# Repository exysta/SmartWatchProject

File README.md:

# SmartWatch Project

## Overview

This repository hosts the source code and technical documentation for the SmartWatch project, developed as part of an embedded systems course. The prototype is a wearable device designed for health monitoring, motion tracking, and real-time data visualization, while seamlessly communicating with a smartphone via Bluetooth Low Energy (BLE).

## Key Features

- **Health Monitoring:** Measures heart rate and blood oxygen saturation (SpO₂) using the MAX30102 sensor.
- **Motion Tracking:** Detects 3D acceleration and orientation with the MPU-6500 sensor.
- **Environmental Sensing:** Captures temperature, humidity, and atmospheric pressure using the BMP280 sensor.
- **GPS Navigation:** Provides accurate location tracking with the NEO-7M module.
- **User Interface:** Displays real-time data on a high-performance ST7789 TFT screen and allows navigation via dedicated buttons.
- **Wireless Communication:** Transmits sensor data using the AT-09 Bluetooth module.
- **Efficient Power Management:** Powered by a rechargeable LiPo battery (USB-C charging) with voltage regulation via LM317.

## Repository Structure

```
smartwatch/
├── hardware/         # Schematics, PCB design files, and hardware documentation
├── Code/         # Source code, drivers, and firmware modules
├── docs/             # Detailed technical documentation, testing procedures, cost calculations, etc.
├── Ressources/         # GIF used for screen animation

└── README.md         # This file
```

## Hardware Overview

The design centers around the STM32L476RCT6 microcontroller, ensuring low power consumption and high performance. The main hardware components include:

- **MCU:** STM32L476RCT6 (ARM Cortex-M4, 80 MHz, low-power design)
- **Bluetooth Module:** AT-09 (based on TI CC2541) for BLE connectivity
- **Sensors:**
  - MPU-6500: IMU for acceleration and gyroscopic data
  - MAX30102: For heart rate and SpO₂ measurements
  - BMP280: For temperature, humidity, and pressure readings
- **Display:** ST7789 TFT screen for real-time information display
- **GPS Module:** NEO-7M for precise location tracking
- **Power Management:** Voltage regulators (LM317) and a power switch optimize energy efficiency

## Software Architecture

The firmware is organized into modular APIs that manage:

- **LED Indicators:** Status and error signals.
- **Bluetooth Communication:** Data exchange over BLE.
- **User Input:** Button handling for reset and display navigation.
- **Sensor Data Acquisition:** Interfaces for reading data via I2C and SPI.

Upon startup, the system performs a handshake with each module. Once all components are verified, the main loop continuously:

- Acquires sensor data on a periodic basis.
- Refreshes the TFT display.
- Monitors user inputs.
- Transmits sensor data via Bluetooth every second.
- Continuously updates GPS data.

## Testing Procedures

Testing covers multiple aspects of the system to ensure reliability:

- **Visual & Hardware Inspection:** Check for soldering issues, short circuits, and proper PCB assembly.
- **Power Supply Testing:** Verify voltage levels and current draw under various loads.
- **Sensor Validation:** Calibrate and compare readings for health, motion, and environmental sensors.
- **Communication Tests:** Ensure robust Bluetooth pairing and accurate GPS data reception.
- **System Integration:** Confirm end-to-end functionality, including data flow from sensors to display and wireless transmission.

## Getting Started

1. **Clone the Repository:**
   ```sh
   git clone https://github.com/exysta/SmartWatchProject.git
   cd SmartWatchProject
   ```
2. **Build the Firmware:**
   - Open the project in STM32CubeIDE or your preferred environment.
   - Compile the project 
4. **Flash the Firmware:**
   - Use an ST-LINK/V2 programmer to flash the firmware onto the STM32 MCU.

## Acknowledgments

- **Project Team:** Mathéo Morin, Lucas Chapart, Mayane Guillon
- **Supervisor:** Marko Kauppinen
- **Course:** Embedded Systems Project

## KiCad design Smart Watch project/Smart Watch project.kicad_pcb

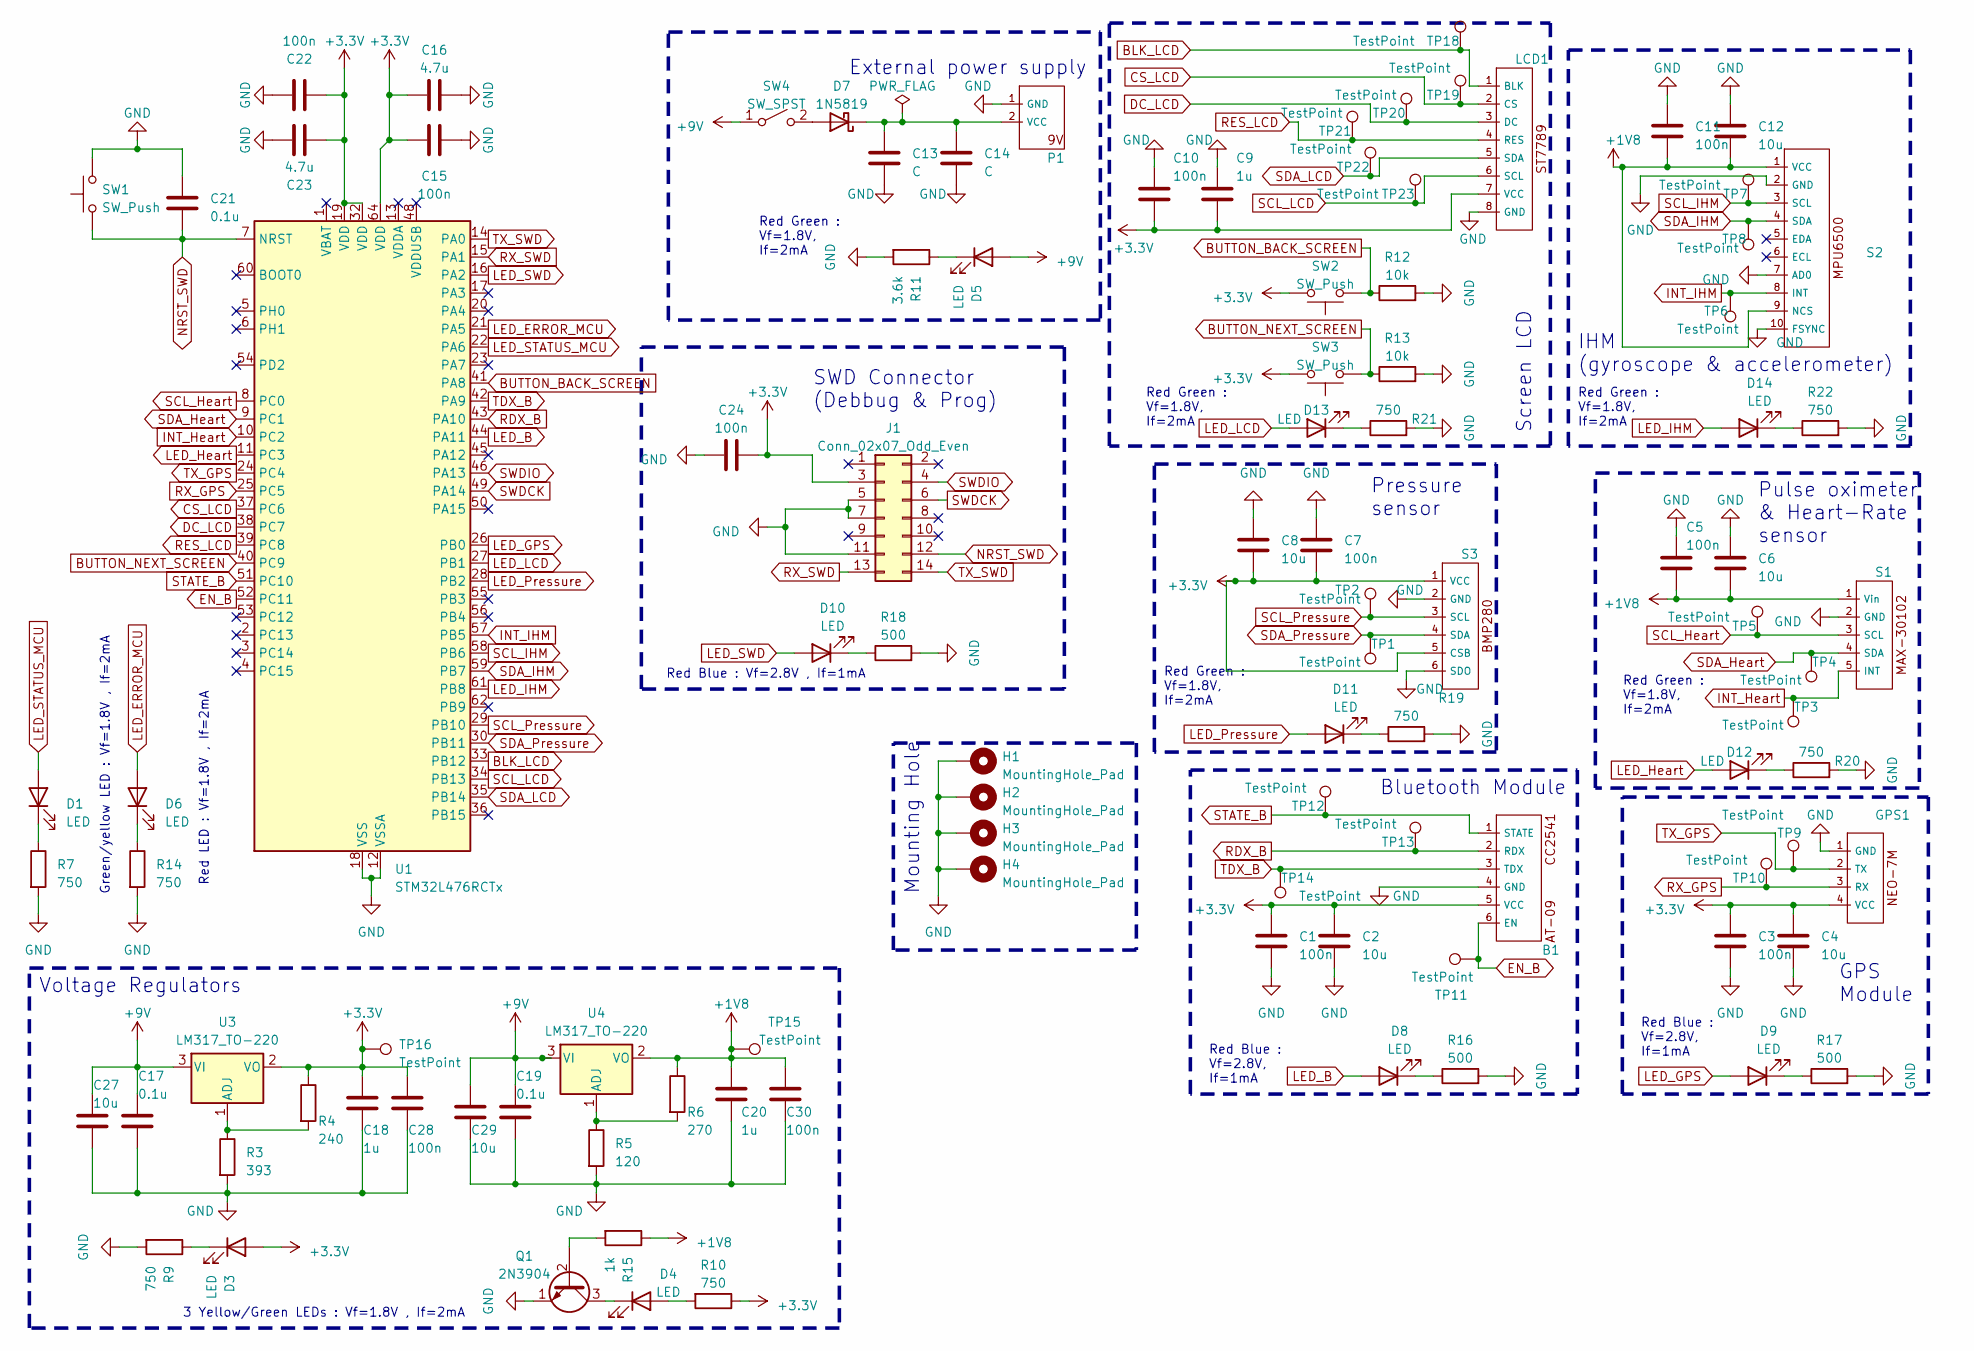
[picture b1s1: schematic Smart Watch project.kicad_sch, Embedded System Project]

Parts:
B1: BL
C1, C3, C5, C7, C10, C11, C15, C22, C24, C28, C30: 100n; C_0805_2012Metric
C2, C4, C6, C8, C12, C27, C29: 10u; C_0805_2012Metric
C9, C18, C20: 1u; C_0805_2012Metric
C13, C14: C; C_0805_2012Metric
C16, C23: 4.7u; C_0805_2012Metric
C17, C19, C21: 0.1u; C_0805_2012Metric
D1, D3, D4, D5, D6, D8, D9, D10, D11, D12, D13, D14: LED; LED_0603_1608Metric
D7: 1N5819; D_DO-41_SOD81_P10.16mm_Horizontal
GPS1: GPS
H1, H2, H3, H4: MountingHole_Pad; MountingHole_2.7mm_Pad_Via
J1: Conn_02x07_Odd_Even; PinHeader_2x07_P1.27mm_Vertical
LCD1: LCD
P1: Power
Q1: 2N3904; TO-92_Inline
R3: 393; R_0805_2012Metric
R4: 240; R_0805_2012Metric
R5: 120; R_0805_2012Metric
R6: 270; R_0805_2012Metric
R7, R9, R10, R14, R19, R20, R21, R22: 750; R_0805_2012Metric
R11: 3.6k; R_0805_2012Metric
R12, R13: 10k; R_0805_2012Metric
R15: 1k; R_0805_2012Metric
R16, R17, R18: 500; R_0805_2012Metric
S1: Heart
S2: IHM
S3: Pressure
SW1, SW2, SW3: SW_Push; SW_PUSH_6mm
SW4: SW_SPST; A11JP_NKK
TP1, TP2, TP3, TP4, TP5, TP6, TP7, TP8, TP9, TP10, TP11, TP12, TP13, TP14, TP15, TP16, TP18, TP19, TP20, TP21, TP22, TP23: TestPoint; TestPoint_Pad_D2.0mm
U1: STM32L476RCTx; LQFP-64_10x10mm_P0.5mm
U3, U4: LM317_TO-220; TO-220-3_Vertical

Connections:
+1V8: C5.1, C6.2, C11.1, C12.2, C20.1, C30.1, R6.1, R15.1, S1.1 (Vin), S2.1 (VCC), S2.9 (NCS), TP15.1, U4.2 (VO)
+3.3V: B1.5 (VCC), C1.1, C2.1, C3.1, C4.1, C7.1, C8.1, C9.1, C10.1, C15.2, C16.2, C18.1, C22.2, C23.2, C24.2, C28.1, D3.2 (A), GPS1.4 (VCC), J1.3, LCD1.7 (VCC), R4.1, R10.1, S3.1 (VCC), S3.5 (CSB), SW2.2, SW3.2, TP16.1, U1.19 (VDD), U1.32 (VDD), U1.64 (VDD), U3.2 (VO)
+9V: C17.1, C19.1, C27.1, C29.1, D5.2 (A), SW4.1 (A), U3.3 (VI), U4.3 (VI)
BLK_LCD: LCD1.1 (BLK), TP18.1, U1.33 (PB12)
BUTTON_BACK_SCREEN: R12.1, SW2.1, U1.41 (PA8)
BUTTON_NEXT_SCREEN: R13.1, SW3.1, U1.40 (PC9)
CS_LCD: LCD1.2 (CS), TP19.1, U1.37 (PC6)
DC_LCD: LCD1.3 (DC), TP20.1, U1.38 (PC7)
EN_B: B1.6 (EN), TP11.1, U1.52 (PC11)
GND: B1.4 (GND), C1.2, C2.2, C3.2, C4.2, C5.2, C6.1, C7.2, C8.2, C9.2, C10.2, C11.2, C12.1, C13.2, C14.2, C15.1, C16.1, C17.2, C18.2, C19.2, C20.2, C21.1, C22.1, C23.1, C24.1, C27.2, C28.2, C29.2, C30.2, GPS1.1 (GND), H1.1, H2.1, H3.1, H4.1, J1.5, J1.7, J1.11, LCD1.8 (GND), P1.1 (GND), Q1.1 (E), R3.2, R5.2, R7.2, R9.2, R11.2, R12.2, R13.2, R14.2, R16.2, R17.2, R18.2, R19.2, R20.2, R21.2, R22.2, S1.2 (GND), S2.2 (GND), S2.7 (AD0), S2.10 (FSYNC), S3.2 (GND), S3.6 (SDO), SW1.2, U1.12 (VSSA), U1.18 (VSS), U1.31 (VSS), U1.47 (VSS), U1.63 (VSS)
INT_Heart: S1.5 (INT), TP3.1, U1.10 (PC2)
INT_IHM: S2.8 (INT), TP6.1, U1.57 (PB5)
LED_B: D8.2 (A), U1.44 (PA11)
LED_ERROR_MCU: D6.2 (A), U1.21 (PA5)
LED_GPS: D9.2 (A), U1.26 (PB0)
LED_Heart: D12.2 (A), U1.11 (PC3)
LED_IHM: D14.2 (A), U1.61 (PB8)
LED_LCD: D13.2 (A), U1.27 (PB1)
LED_Pressure: D11.2 (A), U1.28 (PB2)
LED_STATUS_MCU: D1.2 (A), U1.22 (PA6)
LED_SWD: D10.2 (A), U1.16 (PA2)
NRST_SWD: C21.2, J1.12, SW1.1, U1.7 (NRST)
unnamed: D1.1 (K), R7.1
unnamed: D3.1 (K), R9.1
unnamed: D4.2 (A), R10.2
unnamed: D4.1 (K), Q1.3 (C)
unnamed: D5.1 (K), R11.1
unnamed: D6.1 (K), R14.1
unnamed: D7.2 (A), SW4.2 (B)
unnamed: C13.1, C14.1, D7.1 (K), P1.2 (VCC)
unnamed: D8.1 (K), R16.1
unnamed: D9.1 (K), R17.1
unnamed: D10.1 (K), R18.1
unnamed: D11.1 (K), R19.1
unnamed: D12.1 (K), R20.1
unnamed: D13.1 (K), R21.1
unnamed: D14.1 (K), R22.1
unnamed: Q1.2 (B), R15.2
unnamed: R3.1, R4.2, U3.1 (ADJ)
unnamed: R5.1, R6.2, U4.1 (ADJ)
RDX_B: B1.2 (RDX), TP13.1, U1.43 (PA10)
RES_LCD: LCD1.4 (RES), TP21.1, U1.39 (PC8)
RX_GPS: GPS1.3 (RX), TP10.1, U1.25 (PC5)
RX_SWD: J1.13, U1.15 (PA1)
SCL_Heart: S1.3 (SCL), TP5.1, U1.8 (PC0)
SCL_IHM: S2.3 (SCL), TP7.1, U1.58 (PB6)
SCL_LCD: LCD1.6 (SCL), TP23.1, U1.34 (PB13)
SCL_Pressure: S3.3 (SCL), TP2.1, U1.29 (PB10)
SDA_Heart: S1.4 (SDA), TP4.1, U1.9 (PC1)
SDA_IHM: S2.4 (SDA), TP8.1, U1.59 (PB7)
SDA_LCD: LCD1.5 (SDA), TP22.1, U1.35 (PB14)
SDA_Pressure: S3.4 (SDA), TP1.1, U1.30 (PB11)
STATE_B: B1.1 (STATE), TP12.1, U1.51 (PC10)
SWDCK: J1.6, U1.49 (PA14)
SWDIO: J1.4, U1.46 (PA13)
TDX_B: B1.3 (TDX), TP14.1, U1.42 (PA9)
TX_GPS: GPS1.2 (TX), TP9.1, U1.24 (PC4)
TX_SWD: J1.14, U1.14 (PA0)

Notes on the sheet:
Pressure sensor
Screen LCD
Red Green : Vf=1.8V, If=2mA
Red LED : Vf=1.8V , If=2mA
SWD Connector (Debbug & Prog)
Mounting Hole
Red Blue : Vf=2.8V, If=1mA
Red Blue : Vf=2.8V , If=1mA
GPS Module
3 Yellow/Green LEDs : Vf=1.8V , If=2mA
Pulse oximeter & Heart-Rate sensor
Green/yellow LED : Vf=1.8V , If=2mA
External power supply
Bluetooth Module
Voltage Regulators
IHM (gyroscope & accelerometer)

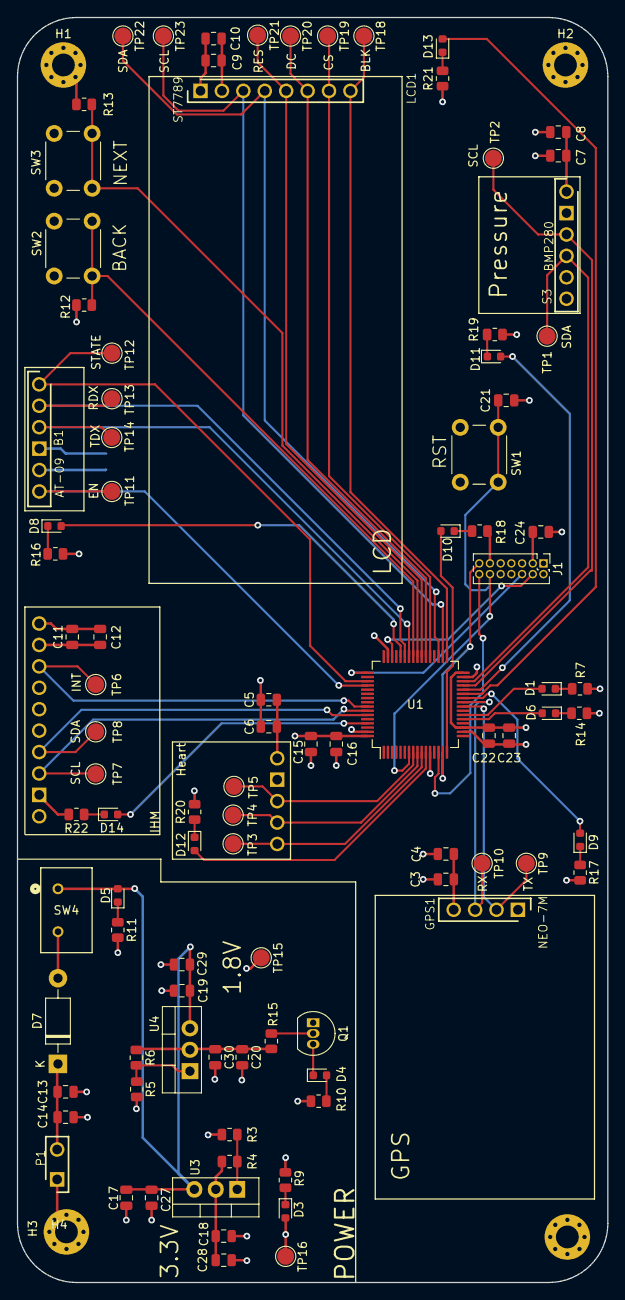
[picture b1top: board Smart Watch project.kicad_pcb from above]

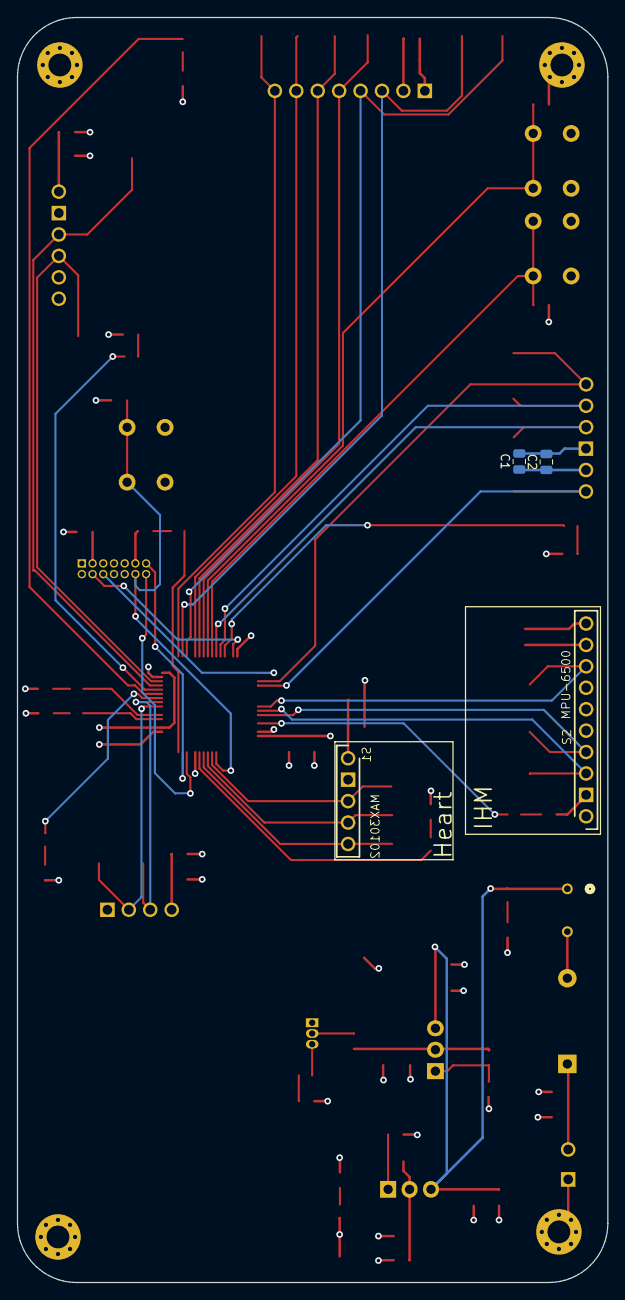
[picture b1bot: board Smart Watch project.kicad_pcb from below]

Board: 6 copper layers, 70.0 x 150.0 mm, 102 parts (4 on the bottom side), 58 nets.

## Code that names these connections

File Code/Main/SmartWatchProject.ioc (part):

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Mcu.Name=STM32L476R(C-E-G)Tx
Mcu.Package=LQFP64
Mcu.UserName=STM32L476RCTx
PA0.GPIOParameters=GPIO_Label
PA0.GPIO_Label=STLINK_TX
PA0.Mode=Asynchronous
PA0.Signal=UART4_TX
PA1.GPIOParameters=GPIO_Label
PA1.GPIO_Label=STLINK_RX
PA1.Mode=Asynchronous
PA1.Signal=UART4_RX
PA10.GPIOParameters=GPIO_Label
PA10.GPIO_Label=BLE_RX
PA10.Mode=Asynchronous
PA10.Signal=USART1_RX
PA11.GPIOParameters=PinState,GPIO_Label
PA11.GPIO_Label=LED_BLE
PA11.PinState=GPIO_PIN_RESET
PA11.Signal=GPIO_Output
PA13\ (JTMS-SWDIO).Mode=Serial_Wire
PA13\ (JTMS-SWDIO).Signal=SYS_JTMS-SWDIO
PA14\ (JTCK-SWCLK).Mode=Serial_Wire
PA14\ (JTCK-SWCLK).Signal=SYS_JTCK-SWCLK
PA2.GPIOParameters=PinState,GPIO_Label
PA2.GPIO_Label=LED_SWD
PA2.PinState=GPIO_PIN_RESET
PA2.Signal=GPIO_Output
PA5.GPIOParameters=PinState,GPIO_Label
PA5.GPIO_Label=LED_ERROR
PA5.PinState=GPIO_PIN_RESET
PA5.Signal=GPIO_Output
PA6.GPIOParameters=PinState,GPIO_Label
PA6.GPIO_Label=LED_STATUS
PA6.PinState=GPIO_PIN_RESET
PA6.Signal=GPIO_Output
PA8.GPIOParameters=GPIO_Label
PA8.GPIO_Label=BUTTON_BACK
PA8.Signal=GPXTI8
PA9.GPIOParameters=GPIO_Label
PA9.GPIO_Label=BLE_TX
PA9.Mode=Asynchronous
PA9.Signal=USART1_TX
PB0.GPIOParameters=PinState,GPIO_Label
PB0.GPIO_Label=LED_GPS
PB0.PinState=GPIO_PIN_RESET
PB0.Signal=GPIO_Output
PB1.GPIOParameters=PinState,GPIO_Label
PB1.GPIO_Label=LED_LCD
PB1.PinState=GPIO_PIN_RESET
PB1.Signal=GPIO_Output
PB10.GPIOParameters=GPIO_Label
PB10.GPIO_Label=BMP280_SCL
PB10.Mode=I2C
PB10.Signal=I2C2_SCL
PB11.GPIOParameters=GPIO_Label
PB11.GPIO_Label=BMP280_SDA
PB11.Mode=I2C
PB11.Signal=I2C2_SDA
PB12.GPIOParameters=GPIO_Label
PB12.GPIO_Label=ST7789_RST
PB12.Signal=GPIO_Output
PB13.GPIOParameters=GPIO_Label
PB13.GPIO_Label=ST7789_SCK
PB13.Mode=TX_Only_Simplex_Unidirect_Master
PB13.Signal=SPI2_SCK
PB14.Signal=GPIO_Analog
PB15.GPIOParameters=GPIO_Label
PB15.GPIO_Label=ST7789_MOSI
PB15.Mode=TX_Only_Simplex_Unidirect_Master
PB15.Signal=SPI2_MOSI
PB2.GPIOParameters=PinState,GPIO_Label
PB2.GPIO_Label=LED_BMP280
PB2.PinState=GPIO_PIN_RESET
PB2.Signal=GPIO_Output
PB5.GPIOParameters=GPIO_Label
PB5.GPIO_Label=MPU6500_INT
PB5.Signal=GPXTI5
PB6.GPIOParameters=GPIO_Label
PB6.GPIO_Label=MPU6500_SCL
PB6.Mode=I2C
PB6.Signal=I2C1_SCL
PB7.GPIOParameters=GPIO_Label
PB7.GPIO_Label=MPU6500_SDA
PB7.Mode=I2C
PB7.Signal=I2C1_SDA
PB8.GPIOParameters=PinState,GPIO_Label
PB8.GPIO_Label=LED_MPUS6500
PB8.PinState=GPIO_PIN_RESET
PB8.Signal=GPIO_Output
PC0.GPIOParameters=GPIO_Label
PC0.GPIO_Label=MAX30102_SCL
PC0.Mode=I2C
PC0.Signal=I2C3_SCL
PC1.GPIOParameters=GPIO_Label
PC1.GPIO_Label=MAX30102_SDA
PC1.Mode=I2C
PC1.Signal=I2C3_SDA
PC10.GPIOParameters=PinState,GPIO_Label,GPIO_ModeDefaultOutputPP
PC10.GPIO_Label=BLE_EN
PC10.GPIO_ModeDefaultOutputPP=GPIO_MODE_OUTPUT_PP
PC10.PinState=GPIO_PIN_RESET
PC10.Signal=GPIO_Output
PC11.GPIOParameters=GPIO_Label
PC11.GPIO_Label=BLE_STATE
PC11.Signal=GPIO_Input
PC2.GPIOParameters=GPIO_PuPd,GPIO_Label,GPIO_ModeDefaultEXTI
PC2.GPIO_Label=MAX30102_INT
PC2.GPIO_ModeDefaultEXTI=GPIO_MODE_IT_FALLING
PC2.GPIO_PuPd=GPIO_PULLUP
PC2.Signal=GPXTI2
PC3.GPIOParameters=PinState,GPIO_Label
PC3.GPIO_Label=LED_MAX30102
PC3.PinState=GPIO_PIN_RESET
PC3.Signal=GPIO_Output
PC4.GPIOParameters=GPIO_Label
PC4.GPIO_Label=GPS_TX
PC4.Mode=Asynchronous
PC4.Signal=USART3_TX
PC5.GPIOParameters=GPIO_Label
PC5.GPIO_Label=GPS_RX
PC5.Mode=Asynchronous
PC5.Signal=USART3_RX
PC6.GPIOParameters=GPIO_Speed,GPIO_Label
PC6.GPIO_Label=ST7789_DC
PC6.GPIO_Speed=GPIO_SPEED_FREQ_HIGH
PC6.Signal=GPIO_Output
PC7.GPIOParameters=GPIO_Label
PC7.GPIO_Label=ST7789_CS
PC7.Signal=GPIO_Output
PC8.GPIOParameters=PinState,GPIO_Label
PC8.GPIO_Label=ST7789_BLK
PC8.PinState=GPIO_PIN_RESET
PC8.Signal=GPIO_Output
PC9.GPIOParameters=GPIO_Label
PC9.GPIO_Label=BUTTON_NEXT
PC9.Signal=GPXTI9
RCC.HSE_VALUE=8000000
RCC.SYSCLKFreq_VALUE=80000000
RCC.SYSCLKSource=RCC_SYSCLKSOURCE_PLLCLK
board=custom

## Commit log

2025-03-10 working UART to Bluettooth module
2025-03-13 working bluetooth for test board
2025-03-17 Kicad
    PCB
2025-03-23 working screen
2025-04-18 working initial connection to MPU6500
2025-04-18 working MPU6500
2025-05-06 working red heart display on screen
2025-05-08 cleaner code to display images
2025-05-09 working weather animation
2025-05-10 functional Heart rate and Environnemental UI
2025-05-12 testing MAX30102 sensor: failing on board + flash PCB success
2025-05-12 porting code to pcb
2025-05-13 working BLE comms, had to invert rx,tx pins
2025-05-13 working GPS clock, swap Rx and Tx
2025-05-13 finishing working on UI
2025-05-17 UART comms added
2025-05-26 gave up on processing hearrate and spo2
2025-05-27 working gps position + time
2025-05-27 working BME280
2025-06-03 print sensor data over bluetooth + STlink
